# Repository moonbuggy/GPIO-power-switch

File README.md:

# GPIO Power Switch
Cut power to a single board computer (SBC) and attached components with a
MOSFET, power on and off with a button, indicate power and booted/ready status
with an LED.

<p><br/>
<em>GPIO Power Switch</em></p>

-   [Rationale](#rationale)
-   [Overview](#overview)
-   [Hardware](#hardware)
    *   [Assembled](#assembled)
    *   [Schematic](#schematic)
    *   [Layout](#layout)
-   [Setup](#setup)
    *   [GPIO shutdown](#gpio-shutdown)
    *   [GPIO power key](#gpio-power-key)
    *   [Ready LED](#ready-led)

There's two different options, with the difference being whether the _ready_
status LED is switched on with a high or low signal from the GPIO pin.

## Rationale
Not all single board computers actually power off when they're shutdown, and
many will continue to power attached devices through the 3.3 and 5V pins on the
GPIO header.

The easiest way to deal with this is to cut power with a switch of our own,
making use of various signals to and from the GPIO supported by the linux kernel
to only cut power when the device has shutdown.

## Overview
This circuit carries out multiple functions:
-   MOSFET SR latch

    When 'reset' the power MOSFET is switched on, connecting the load to ground.
    When 'set' the power MOSFET is switched off, disconnecting the load from
    ground.

-   Push button

    If the MOSFET is off, when pressed 'resets' the MOSFET, connecting the SBC
    to ground and causing the SBC to boot. If the MOSFET is on, when pressed
    signals the SBC to shutdown by sending a _KEY_POWER_ event code via the GPIO.

-   Status LED

    Red when the MOSFET is switched on by default, can be changed to green with
    a GPIO signal to indicate the devices is booted, a particular system
    service has started, or whatever other criteria is set in software to toggle
    the relevant GPIO pin.

The basic connection between this circuit and the SBC involves three GPIO pins
and looks like this:
<p><br/>
<em>Wiring overview</em></p>

The key thing to note is that the SBC runs off _GND_switched_.

This switch should work with any device that has a GPIO and supports
[gpio-poweroff][gpio-poweroff.txt] (to send a signal when shutdown is complete)
and [gpio-keys][gpio-keys.txt] (to accept a _KEY_POWER_ signal from the push
button).

## Hardware
### Assembled
<p><br/>
<em>Assembled (ready high)</em></p>

### Schematic
There's three main sections of the circuit:

-   An SR latch handles cutting the power and retaining the state
-   A board for the button and LED, to mount on a panel
-   An interface between the GPIO and the other components

The latch is common to both the _ready high_ and _ready low_ circuits, but the
other sections differ.

<p><br/>
<em>SR latch schematic</em></p>

<p><br/>
<em>panel (ready low) schematic</em></p>

<p><br/>
<em>interface (ready low) schematic</em></p>

<p><br/>
<em>panel (ready high) schematic</em></p>

<p><br/>
<em>interface (ready high) schematic</em></p>

### Layout
<p><br/>
<em>ready low front layout</em></p>

<p><br/>
<em>ready low back layout</em></p>

<p><br/>
<em>ready high front layout</em></p>

<p><br/>
<em>ready high back layout</em></p>

In this layout the push button and LED are mounted on a separate board from the
rest of the circuit, which allows easy mounting on a panel in an enclosure.
Obviously the layout can be changed as needed for any intended application.

> [!NOTE]
> The connecting cable between the two boards is not straight-through in this
> layout. Routing tracks on the prototype board is easier if the two boards are
> independent of each other in that regard, leaving the cable to handle routing
> between them.

## Setup
### GPIO shutdown
The _gpio-shutdown_ signal should be active high. Sending a 3.3V signal to
indicate we're shutdown (as opposed to pulling the pin low to ground) makes
sense because once the MOSFET cuts power to the SBC this high signal will fall
back to low.

This is important because the behaviour of the SR latch is undefined when both
_set_ and _reset_ are true at the same time, so we need the _gpio-shutdown_
signal from the GPIO to be low/false when it comes time to restore power, to
ensure the push button can reliably toggle the latch.

> [!NOTE]
> The _GPIO_SHUTDOWN_ signal requires `CONFIG_POWER_RESET_GPIO` and
> `CONFIG_POWER_RESET_GPIO_RESTART` to be enabled in the kernel, which may not
> be the case for a default OS install.

An example device tree overlay (from the
[moonbuggy/Orange-Pi-Zero-GPS-NTP][moonbuggy/Orange-Pi-Zero-GPS-NTP] project) is
available at [overlays/sun8i-h3-gpio-poweroff.dts](overlays/sun8i-h3-gpio-poweroff.dts).
In this example we're using pin 21 (_PA16_) on the Orange Pi Zero.

Reference: [gpio-poweroff.txt][gpio-poweroff.txt]

### GPIO power key
When the push button is pressed it will pull a GPIO pin to ground. Using
_gpio-keys_ we can create a device tree overlay to configure this pin as an input
key and assign a _KEY_POWER_ event code. (All available event codes are listed in
[include/uapi/linux/input-event-codes.h](https://git.kernel.org/pub/scm/linux/kernel/git/torvalds/linux.git/tree/include/uapi/linux/input-event-codes.h).)

An example overlay (also from the
[moonbuggy/Orange-Pi-Zero-GPS-NTP][moonbuggy/Orange-Pi-Zero-GPS-NTP] project) is
available at [overlays/gpio-key-power.dts](overlays/gpio-key-power.dts). In this
example we're using pin 12 (_PA07_) on the Orange Pi Zero, with _116_ being the
numeric code for _KEY_POWER_.

Reference: [gpio-keys.txt][gpio-keys.txt]

### Ready LED
Using a dual-colour LED, we have a default 'powered' indicator (red) that is on
whenever the power MOSFET is on. A high or low signal (depending on which board
is built) from a GPIO pin will switch this colour off and turn the second colour
(green) on, giving us a 'ready' signal.

The intention is that the change in LED colour should be triggered by software
and indicate that the OS is booted, a service has started or some other specific
condition has been met and the device is usable.

The simplest way to manage this is with a _systemd_ service executing `gpioset`
commands at appropriate times. Once again,
[moonbuggy/Orange-Pi-Zero-GPS-NTP][moonbuggy/Orange-Pi-Zero-GPS-NTP]
provides an example in the
[Status LED section](https://github.com/moonbuggy/Orange-Pi-Zero-GPS-NTP#status-led).
In this application, the device is considered 'ready' once _chrony_ and _gpsd_
are running and we're using pin 16 (_PA19_) for the signal.

The current limiting resistors will need to be adjusted for the specific LED in
use and the desired brightness.

[moonbuggy/Orange-Pi-Zero-GPS-NTP]: https://github.com/moonbuggy/Orange-Pi-Zero-GPS-NTP
[gpio-poweroff.txt]: https://www.kernel.org/doc/Documentation/devicetree/bindings/power/reset/gpio-poweroff.txt
[gpio-keys.txt]: https://www.kernel.org/doc/Documentation/devicetree/bindings/input/gpio-keys.txt

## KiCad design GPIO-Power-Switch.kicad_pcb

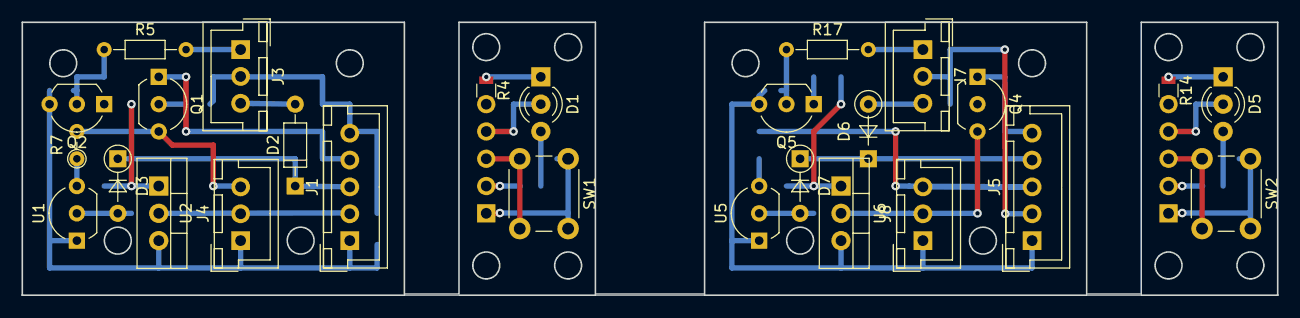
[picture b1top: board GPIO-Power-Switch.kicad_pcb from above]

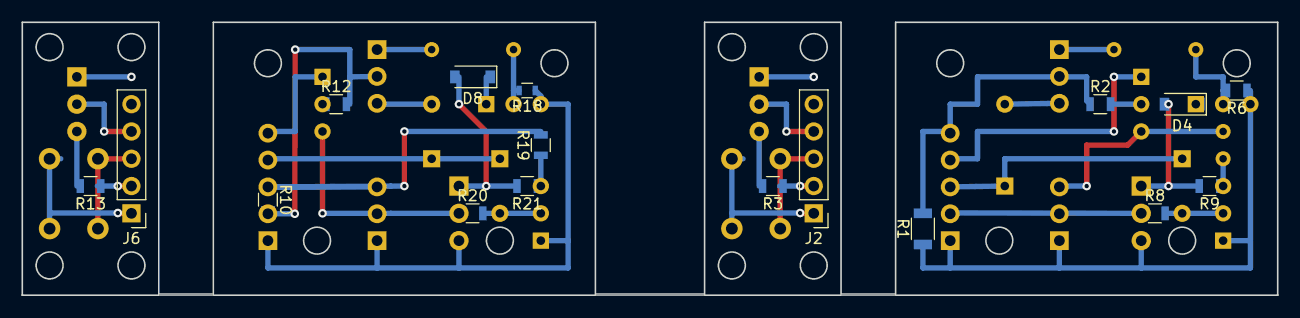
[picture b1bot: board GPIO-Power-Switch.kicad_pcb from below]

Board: 2 copper layers, 116.8 x 25.4 mm, 44 parts (17 on the bottom side), 27 nets.

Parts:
D1, D5: Red/Green; LED_D3.0mm-3
D2: BAT48; D_DO-35_SOD27_P7.62mm_Horizontal
D3, D7: BAT48; D_DO-35_SOD27_P5.08mm_Vertical_AnodeUp
D4, D8: B0520LW; D_SOD-123
D6: BAT48; D_DO-35_SOD27_P5.08mm_Vertical_KathodeUp
J1, J5: Pannel_Out; JST_XH_B05B-XH-A_05x2.50mm_Straight
J2, J6: Panel_In; Pin_Header_Straight_1x05_Pitch2.54mm
J3, J7: GPIO; JST_XH_B03B-XH-A_03x2.50mm_Straight
J4, J8: Power; JST_XH_B03B-XH-A_03x2.50mm_Straight
Q1: BS208; TO-92_Inline_Wide
Q2, Q4, Q5: BS170; TO-92_Inline_Wide
R1: 1M; R_1206
R2, R3, R8, R9, R12, R13, R19, R20, R21: 10k; R_0805
R4, R14: 4k7; R_0805
R5, R17: 10k; R_Axial_DIN0204_L3.6mm_D1.6mm_P7.62mm_Horizontal
R6, R10: 1M; R_0805
R7: 10k; R_Axial_DIN0204_L3.6mm_D1.6mm_P2.54mm_Vertical
R18: 1M; R_0603
SW1, SW2: SW_Push; SW_PUSH_6mm
U1, U5: 2N7000; TO-92_Inline_Wide
U2, U6: IRL540N; TO-220-3_Vertical

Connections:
(not)Reset: D2.1, D3.1, D6.1, D7.1, J1.3, J2.3, J5.4, J6.3, SW1.2, SW2.2
(not)Set: D4.1, D8.1, Q2.1, Q5.1
+5V: D5.2, J4.3, J5.3, J6.4, J8.3, Q1.3, R7.2, R10.1, R19.2
/Power Switch (active low leds)/GPIO_SHUTDOWN: J7.1, R17.2
/Power Switch (active low leds)/KEY_POWER: D6.2, J7.3
/Power Switch (active low leds)/NQ: R19.1, R21.1, U5.3
/Power Switch (active low leds)/READY_SIGNAL: J5.2, J6.5, J7.2, R10.2, R12.2, R14.2
/Power Switch (active low leds)/green: D5.1, R14.1
/Power Switch (active low leds)/red: J5.5, J6.2, Q4.1, R13.1
/Power Switch/GPIO_SHUTDOWN: J3.1, R5.2
/Power Switch/KEY_POWER: D2.2, J3.3
/Power Switch/NQ: R7.1, R9.1, U1.3
/Power Switch/READY_SIGNAL: J1.5, J2.5, J3.2, R1.2, R2.1, R4.2
/Power Switch/green: D1.1, R4.1
/Power Switch/red: J1.4, J2.2, Q1.1, R3.1
GND: J1.1, J2.1, J4.1, J5.1, J6.1, J8.1, Q2.3, Q5.3, R1.1, R6.1, R18.1, SW1.1, SW2.1, U1.1, U2.3, U5.1, U6.3
GND_SWITCHED: D1.2, J1.2, J2.4, J4.2, J8.2, Q4.3, R8.1, R20.1, U2.2, U6.2
unnamed: D1.3, R3.2
unnamed: D3.2, R8.2, U1.2
unnamed: D4.2, R9.2, U2.1
unnamed: D5.3, R13.2
unnamed: D7.2, R20.2, U5.2
unnamed: D8.2, R21.2, U6.1
unnamed: Q1.2, R2.2
unnamed: Q2.2, R5.1, R6.2
unnamed: Q4.2, R12.1
unnamed: Q5.2, R17.1, R18.2

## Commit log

2024-04-18 fixed typo
